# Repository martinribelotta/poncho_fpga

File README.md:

# FPGA Poncho para EDU CIAA

Poncho FPGA basado en la placa [Olimex iCE40HX1K-EVB](https://www.olimex.com/Products/FPGA/iCE40/iCE40HX1K-EVB/open-source-hardware)

> Licencia Apache 2.0 relicenciable a CIAA 1.0

## Caracteristicas
  - FPGA iCE40HX4K soportada por el proyecto IceStorm
  - 8-64MB de SDRAM
  - 64Mb SPI flash
  - Oscilador 50/100MHz on board
  - 52 I/O digitales 

## Lista de tareas
  - [x] Esqematico preeliminar
  - [x] Revision del esquematico
  - [x] Asignado de footprints
  - [x] Place and route
  - [x] Archivos de fabricacion
  - [x] Fabricación del PCB
  - [x] BOM (TBC)
  - [ ] Montaje y test

## Schematic

## Board preview

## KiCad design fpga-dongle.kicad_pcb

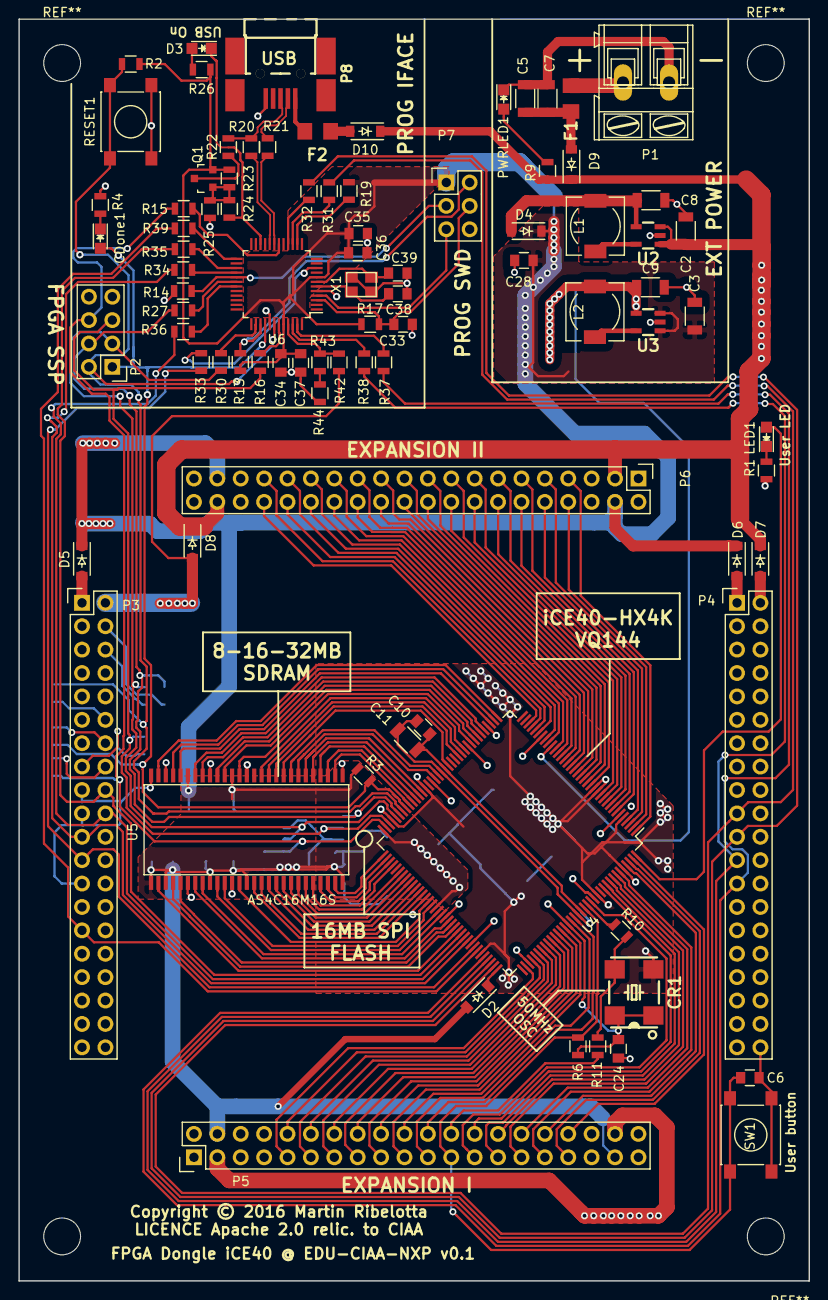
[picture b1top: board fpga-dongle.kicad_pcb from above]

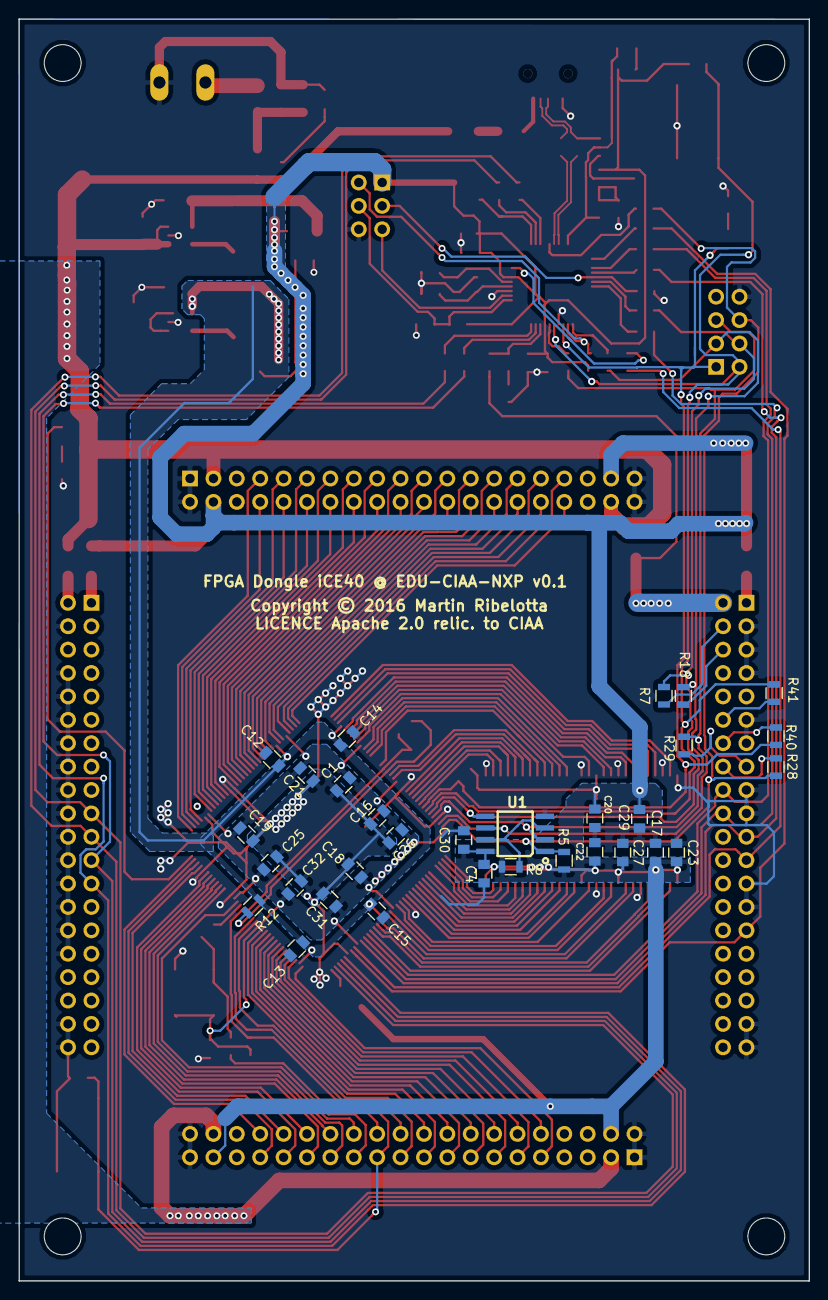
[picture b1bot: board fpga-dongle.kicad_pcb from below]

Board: 2 copper layers, 85.8 x 137.0 mm, 118 parts (31 on the bottom side), 169 nets.

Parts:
C1, C4, C6, C10, C12, C13, C14, C15, C16, C17, C18, C19, C20, C21, C22, C23, C24, C25, C26, C27, C28, C29, C30, C31, C32, C33, C34, C36: 100nF; C_0805
C2, C3: 22uF; C_1206
C5, C7: 47uF; C_1206
C8, C9, C11: 10uF; C_1206
C35, C37: 10nF; C_0805
C38, C39: 18pF; C_0805
CDone1: LED/Green/0805; LED-0805
CR1: Oscillator-50MHZ_TXC-7W; Oscillator_7.0x5.0mm
D2, D4, D5, D6, D7, D8, D9, D10: 1N5819(S4SOD-123); SOD-123
D3: LED/Red/0805; LED-0805
F1, F2: 1A; FUSE-1206
L1, L2: 2.2uH; Choke_SMD_6.3x6.3_H3
LED1: LED/Red/0805; LED-0805
P1: CONN_01X02; AK300-2
P2: PGM; Pin_Header_Straight_2x04
P3: right; Pin_Header_Straight_2x20
P4: left; Pin_Header_Straight_2x20
P5, P6: CONN_01X40; Pin_Header_Straight_2x20
P7: DBG_SWD; Pin_Header_Straight_2x03
P8: USB_PWR; USB_Mini-B-NOSILK
PWRLED1: LED/Red/0805; LED-0805
Q1: BC857; SOT-23
R1, R3, R9, R19, R24, R26: 2.2k; R_0805
R2, R5, R6, R8, R13, R14, R17, R23, R42, R43, R44: 10k; R_0805
R4, R10, R11, R15, R16, R27, R30: 22R; R_0805
R7, R12, R18, R28, R29, R31, R32, R33, R34, R35, R36, R37, R38, R39, R40, R41: 100R; R_0805
R20, R21: 33R; R_0805
R22: 1.5k; R_0805
R25: UL; R_0805
RESET1: T1107A(6x3,8x2,5MM); SW_SPST_PTS645
SW1: T1107A(6x3,8x2,5MM); SW_SPST_PTS645
U1: W25Q128FVSIG(SOIC-8_208mil); SOIC-8_208mil
U2: sc189(Z) 3.3v; SOT-23-5
U3: sc189(C) 1.2v; SOT-23-5
U4: iCE40-HX4K-TQ144; LQFP-144_20x20mm_Pitch0.5mm
U5: AS4C16M16S; TSOP_II_54
U6: LPC11U35FBD48; LQFP-48_7x7mm_Pitch0.5mm
X1: 12MHz; crystal_FA238-TSX3225

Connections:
+1V2: C9.2, C12.1, C13.1, C14.1, C15.1, L2.2, R12.1, U3.4, U4.27, U4.40, U4.92, U4.111
+3V3: C1.2, C3.2, C4.2, C16.1, C17.1, C18.1, C19.1, C20.1, C21.1, C22.1, C23.1, C24.1, C25.1, C26.1, C27.1, C28.1, C29.1, C30.1, C31.1, C32.1, C34.1, C35.1, C36.1, C37.1, CR1.1, CR1.4, D2.2, D4.1, D5.1, D6.1, P5.4, P5.37, P6.4, P6.37, P7.1, Q1.2, R2.2, R3.2, R5.2, R6.2, R8.1, R13.1, R17.1, R19.2, R23.1, R26.1, U1.8, U3.1, U3.3, U4.6, U4.30, U4.46, U4.57, U4.72, U4.89, U4.100, U4.123, U4.131, U5.1, U5.3, U5.9, U5.14, U5.27, U5.43, U5.49, U6.8, U6.44
+5V: C2.2, D7.1, D8.1, D9.1, D10.1, P5.3, P5.38, P6.3, P6.38, R9.1, U2.1, U2.3
/AUX_CDONE: P3.14, R40.1
/AUX_CRESET: P3.12, R41.1
/AUX_SPI_MISO: P3.4, R7.1
/AUX_SPI_MOSI: P3.6, R18.1
/AUX_SPI_SCK: P3.15, R29.1
/AUX_SPI_SSEL: P3.16, R28.1
/BUT1: C6.2, P5.23, R6.1, SW1.2, U4.128
/CIAA_3V3_1: D6.2, P4.1
/CIAA_3V3_2: D5.2, P3.1
/CIAA_5V1: D7.2, P4.2
/CIAA_5V2: D8.2, P3.2, R42.2
/DBG_SWCLK: P7.3, R14.1, U6.29
/DBG_SWDIO: P7.2, R13.2, U6.39
/DBG_~ISP~: P7.5, U6.4
/DBG_~RST~: C33.1, P7.4, R17.2, U6.3
/D_USB_N: R21.2, U6.19
/D_USB_P: R20.2, U6.20
/EXTCLK: P5.24, R11.1
/FPGA_IO_BANK1_0: P5.9, U4.110
/FPGA_IO_BANK1_1: P5.10, U4.112
/FPGA_IO_BANK1_2: P5.11, U4.113
/FPGA_IO_BANK1_3: P5.12, U4.114
/FPGA_IO_BANK1_4: P5.13, U4.115
/FPGA_IO_BANK1_5: P5.14, U4.116
/FPGA_IO_BANK1_6: P5.15, U4.117
/FPGA_IO_BANK1_7: P5.16, U4.118
/FPGA_IO_BANK1_8: P5.17, U4.119
/FPGA_IO_BANK1_9: P5.18, U4.120
/FPGA_IO_BANK1_10: P5.19, U4.121
/FPGA_IO_BANK1_11: P5.20, U4.122
/FPGA_IO_BANK1_12: P5.21, U4.124
/FPGA_IO_BANK1_13: P5.22, U4.125
/FPGA_IO_BANK1_14: P5.25, U4.130
/FPGA_IO_BANK1_15: P5.26, U4.134
/FPGA_IO_BANK1_16: P5.27, U4.135
/FPGA_IO_BANK1_17: P5.28, U4.136
/FPGA_IO_BANK1_18: P5.29, U4.137
/FPGA_IO_BANK1_19: P5.30, U4.138
/FPGA_IO_BANK1_20: P5.31, U4.139
/FPGA_IO_BANK1_21: P5.32, U4.141
/FPGA_IO_BANK1_22: P5.33, U4.142
/FPGA_IO_BANK1_23: P5.34, U4.143
/FPGA_IO_BANK2_0: P6.7, U4.1
/FPGA_IO_BANK2_1: P6.8, U4.2
/FPGA_IO_BANK2_2: P6.9, U4.3
/FPGA_IO_BANK2_3: P6.10, U4.4
/FPGA_IO_BANK2_4: P6.11, U4.7
/FPGA_IO_BANK2_5: P6.12, U4.8
/FPGA_IO_BANK2_6: P6.13, U4.9
/FPGA_IO_BANK2_7: P6.14, U4.10
/FPGA_IO_BANK2_8: P6.15, U4.11
/FPGA_IO_BANK2_9: P6.16, U4.12
/FPGA_IO_BANK2_10: P6.17, U4.15
/FPGA_IO_BANK2_11: P6.18, U4.16
/FPGA_IO_BANK2_12: P6.19, U4.17
/FPGA_IO_BANK2_13: P6.20, U4.18
/FPGA_IO_BANK2_14: P6.21, U4.19
/FPGA_IO_BANK2_15: P6.22, U4.20
/FPGA_IO_BANK2_16: P6.23, U4.21
/FPGA_IO_BANK2_17: P6.24, U4.22
/FPGA_IO_BANK2_18: P6.25, U4.23
/FPGA_IO_BANK2_19: P6.26, U4.24
/FPGA_IO_BANK2_20: P6.27, U4.25
/FPGA_IO_BANK2_21: P6.28, U4.26
/FPGA_IO_BANK2_22: P6.29, U4.28
/FPGA_IO_BANK2_23: P6.30, U4.29
/FPGA_IO_BANK2_24: P6.31, U4.31
/FPGA_IO_BANK2_25: P6.32, U4.32
/FPGA_IO_BANK2_26: P6.33, U4.33
/FPGA_IO_BANK2_27: P6.34, U4.34
/FPGM_MISO: R27.1, U6.30
/FPGM_MOSI: R30.1, U6.38
/FPGM_SCK: R16.1, U6.43
/FPGM_SS: R15.1, U6.18
/GNDPLL: C10.1, C11.1, U4.53, U4.127
/GPIO0: P3.29, R39.2, U4.102
/I2C_SCL: P4.21, R32.2, U4.106
/I2C_SDA: P4.19, R31.2, U4.107
/LED1: LED1.2, U4.144
/P_GPIO: R39.1, U6.25
/P_RxD: R38.1, U6.46
/P_SCL: R32.1, U6.16
/P_SDA: R31.1, U6.15
/P_SPI_CLK: R36.1, U6.31
/P_SPI_MISO: R35.1, U6.27
/P_SPI_MOSI: R34.1, U6.28
/P_SPI_SS: R33.1, U6.10
/P_TxD: R37.1, U6.47
/RAM_A1: U4.76, U5.23
/RAM_A2: U4.75, U5.24
/RAM_A3: U4.74, U5.25
/RAM_A4: U4.73, U5.26
/RAM_A5: U4.64, U5.29
/RAM_A6: U4.63, U5.30
/RAM_A7: U4.62, U5.31
/RAM_A8: U4.61, U5.32
/RAM_A9: U4.60, U5.33
/RAM_A10: U4.56, U5.34
/RAM_A11: U4.78, U5.22
/RAM_A12: U4.55, U5.35
/RAM_A13: U4.52, U5.36
/RAM_A14: U4.80, U5.20
/RAM_A15: U4.79, U5.21
/RAM_CAS: U4.83, U5.17
/RAM_CKE: U4.49, U5.37
/RAM_CLK: U4.48, U5.38
/RAM_CS: U4.81, U5.19
/RAM_D0: U4.96, U5.2
/RAM_D1: U4.95, U5.4
/RAM_D2: U4.94, U5.5
/RAM_D3: U4.93, U5.7
/RAM_D4: U4.91, U5.8
/RAM_D5: U4.90, U5.10
/RAM_D6: U4.88, U5.11
/RAM_D7: U4.87, U5.13
/RAM_D8: U4.45, U5.42
/RAM_D9: U4.44, U5.44
/RAM_D10: U4.43, U5.45
/RAM_D11: U4.42, U5.47
/RAM_D12: U4.41, U5.48
/RAM_D13: U4.39, U5.50
/RAM_D14: U4.38, U5.51
/RAM_D15: U4.37, U5.53
/RAM_DQMH: U4.47, U5.39
/RAM_DQML: U4.85, U5.15
/RAM_RAS: U4.82, U5.18
/RAM_RDnWR: U4.84, U5.16
/RxD: P4.23, R38.2, U4.105
/SPI_CLK: P3.20, R36.2, U4.98
/SPI_CS: P3.23, R33.2, U4.101
/SPI_MISO: P3.18, R35.2, U4.97
/SPI_MOSI: P3.21, R34.2, U4.99
/SYSCLK: R10.1, U4.129
/TxD: P4.25, R37.2, U4.104
/USB_N: P8.2, R21.1
/USB_P: P8.3, R20.1, R22.1
/VCCPLL: C10.2, C11.2, R12.2, U4.54, U4.126
/iCE40-CDONE: CDone1.2, P2.1, R3.1, R40.2, U4.65, U6.40
/iCE40-CRESET: P2.2, R2.1, R41.2, RESET1.2, U4.66, U6.42
/iCE40-SCK: P2.5, R16.2, R29.2, U1.6, U4.70
/iCE40-SDI: P2.3, R18.2, R30.2, U1.2, U4.68
/iCE40-SDO: P2.4, R7.2, R27.2, U1.5, U4.67
/iCE40-SS_B: P2.6, R5.1, R15.2, R28.2, U1.1, U4.71
/~USB_CONNECT~: D3.1, R24.2, U6.22
GND: C1.1, C2.1, C3.1, C4.1, C5.1, C6.1, C7.1, C8.1, C9.1, C12.2, C13.2, C14.2, C15.2, C16.2, C17.2, C18.2, C19.2, C20.2, C21.2, C22.2, C23.2, C24.2, C25.2, C26.2, C27.2, C28.2, C29.2, C30.2, C31.2, C32.2, C33.2, C34.2, C35.2, C36.2, C37.2, C38.2, C39.2, CR1.2, P1.1, P2.8, P3.3, P3.5, P3.7, P3.11, P3.13, P3.17, P3.19, P3.25, P3.27, P3.37, P3.39, P4.4, P4.8, P4.10, P4.12, P4.14, P4.16, P4.18, P4.20, P4.22, P4.24, P4.26, P4.28, P4.30, P4.32, P4.38, P4.40, P5.1, P5.2, P5.39, P5.40, P6.1, P6.2, P6.39, P6.40, P7.6, P8.5, PWRLED1.1, R1.2, R4.2, R14.2, R25.2, R44.1, RESET1.1, SW1.1, U1.4, U2.2, U3.2, U4.5, U4.13, U4.14, U4.59, U4.69, U4.86, U4.103, U4.132, U4.140, U5.6, U5.12, U5.28, U5.41, U5.46, U5.52, U5.54, U6.5, U6.41, X1.3
unnamed: C5.2, C7.2, D9.2, F1.2
unnamed: C8.2, D4.2, L1.2, U2.4
unnamed: C38.1, U6.6, X1.2
unnamed: C39.1, U6.7, X1.1
unnamed: CDone1.1, R4.1
unnamed: CR1.3, R10.2, R11.2
unnamed: D2.1, U4.108
unnamed: D3.2, R26.2
unnamed: D10.2, F2.2
unnamed: F1.1, P1.2
unnamed: F2.1, P8.1
unnamed: L1.1, U2.5
unnamed: L2.1, U3.5
unnamed: LED1.1, R1.1
unnamed: PWRLED1.2, R9.2
unnamed: Q1.1, R23.2, R24.1, R25.1
unnamed: Q1.3, R22.2
unnamed: R8.2, U1.3, U1.7
unnamed: R19.1, U6.14
unnamed: R42.1, R43.1, U6.45
unnamed: R43.2, R44.2

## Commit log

2016-07-23 Add licence and readme with some images
2016-07-23 Add gitignore
2016-07-24 Assigned componets, first partial place
2016-09-12 First 144LQFP version. To be revised
2016-09-13 First component assign and preeliminar place
2016-09-20 Added SPI programmer with LPC11U35 as MSC
2016-09-20 Update schematics and coumentation
2016-09-23 Reroute SDRAM, connect to EDU-CIAA conenctor, fix schematic net tames
2016-09-24 More route (PWR net connectors TODO)
2016-09-24 First DRC pass. Remain unconenct some 3v3 and 5v
2016-09-25 Fix CIAA connector side error, power net route
2016-09-26 Fix CIAA connector side. Reroute bad lines. First DRC of PCB
2016-09-26 Update docs, create board preview images
2016-09-29 Fix 2V5 net diode from 1v2 to 3v3
2016-09-29 Update doc
2016-09-29 Update doc 2
2016-10-02 Add miltiple power source handling, reroute pertinent nets
2016-10-07 Change USB power-only connector by screw connector
2016-10-07 PCB annotations
2016-10-07 Partial rework of changes lost in last conflict
2016-10-09 More PCB annotations, some rework on GND plane
2016-10-15 Copyright label on board
2016-10-15 Copyright info on bottom sylkscreen
2016-10-19 Correct SDRAM footprint, add mounting joles, first gerber for cuotation
2016-10-30 Add Edge cut to gerbers
2016-11-08 Verified gerbers from OurPCB
2017-01-21 Remove unnecesary components and clean power supply

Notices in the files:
fpga-dongle.kicad_pcb:
Copyright © 2016 Martin Ribelotta
